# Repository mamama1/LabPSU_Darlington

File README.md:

# LabPSU_Darlington

Welcome to my Lab PSU project, which is based on a pair of BD139/TIP3055 Darlingtons and the Teensy 3.5 (3.6 should work as well).<br><br>

This project has been heavily inspired by the original µSupply project by Dave Jones from the EEVBlog.<br>
Link: https://www.eevblog.com/projects/usupply/ <br><br>

Specs:<br>
0 - 16.384V output controllable in 1mV steps<br>
0 - 4096 mA output controllable in 1mA steps<br>
Around 0.1% accuracy due to high accuracy components<br>
16 Bit DACs (DAC8311)<br>
High precision voltage reference for the DACs (REF5040)
16 Bit ADCs (ADS1115)<br>
Low Ripple, Low Noise<br>
25kHz PWM/temperature controlled Fan output for standard PWM capable FANs<br>
One Board solution (toroidal transformer not onboard)<br>
Optional Front Panel for Display, rotary encoder, button and LED mounting<br>
Fast UI thanks to Teensy's 120 MHz frequency<br>
Header for ESP8266, ESP32 or basically any other UART compatible device, including 3.3V and GND as well as two I/O pins (one PWM capable)

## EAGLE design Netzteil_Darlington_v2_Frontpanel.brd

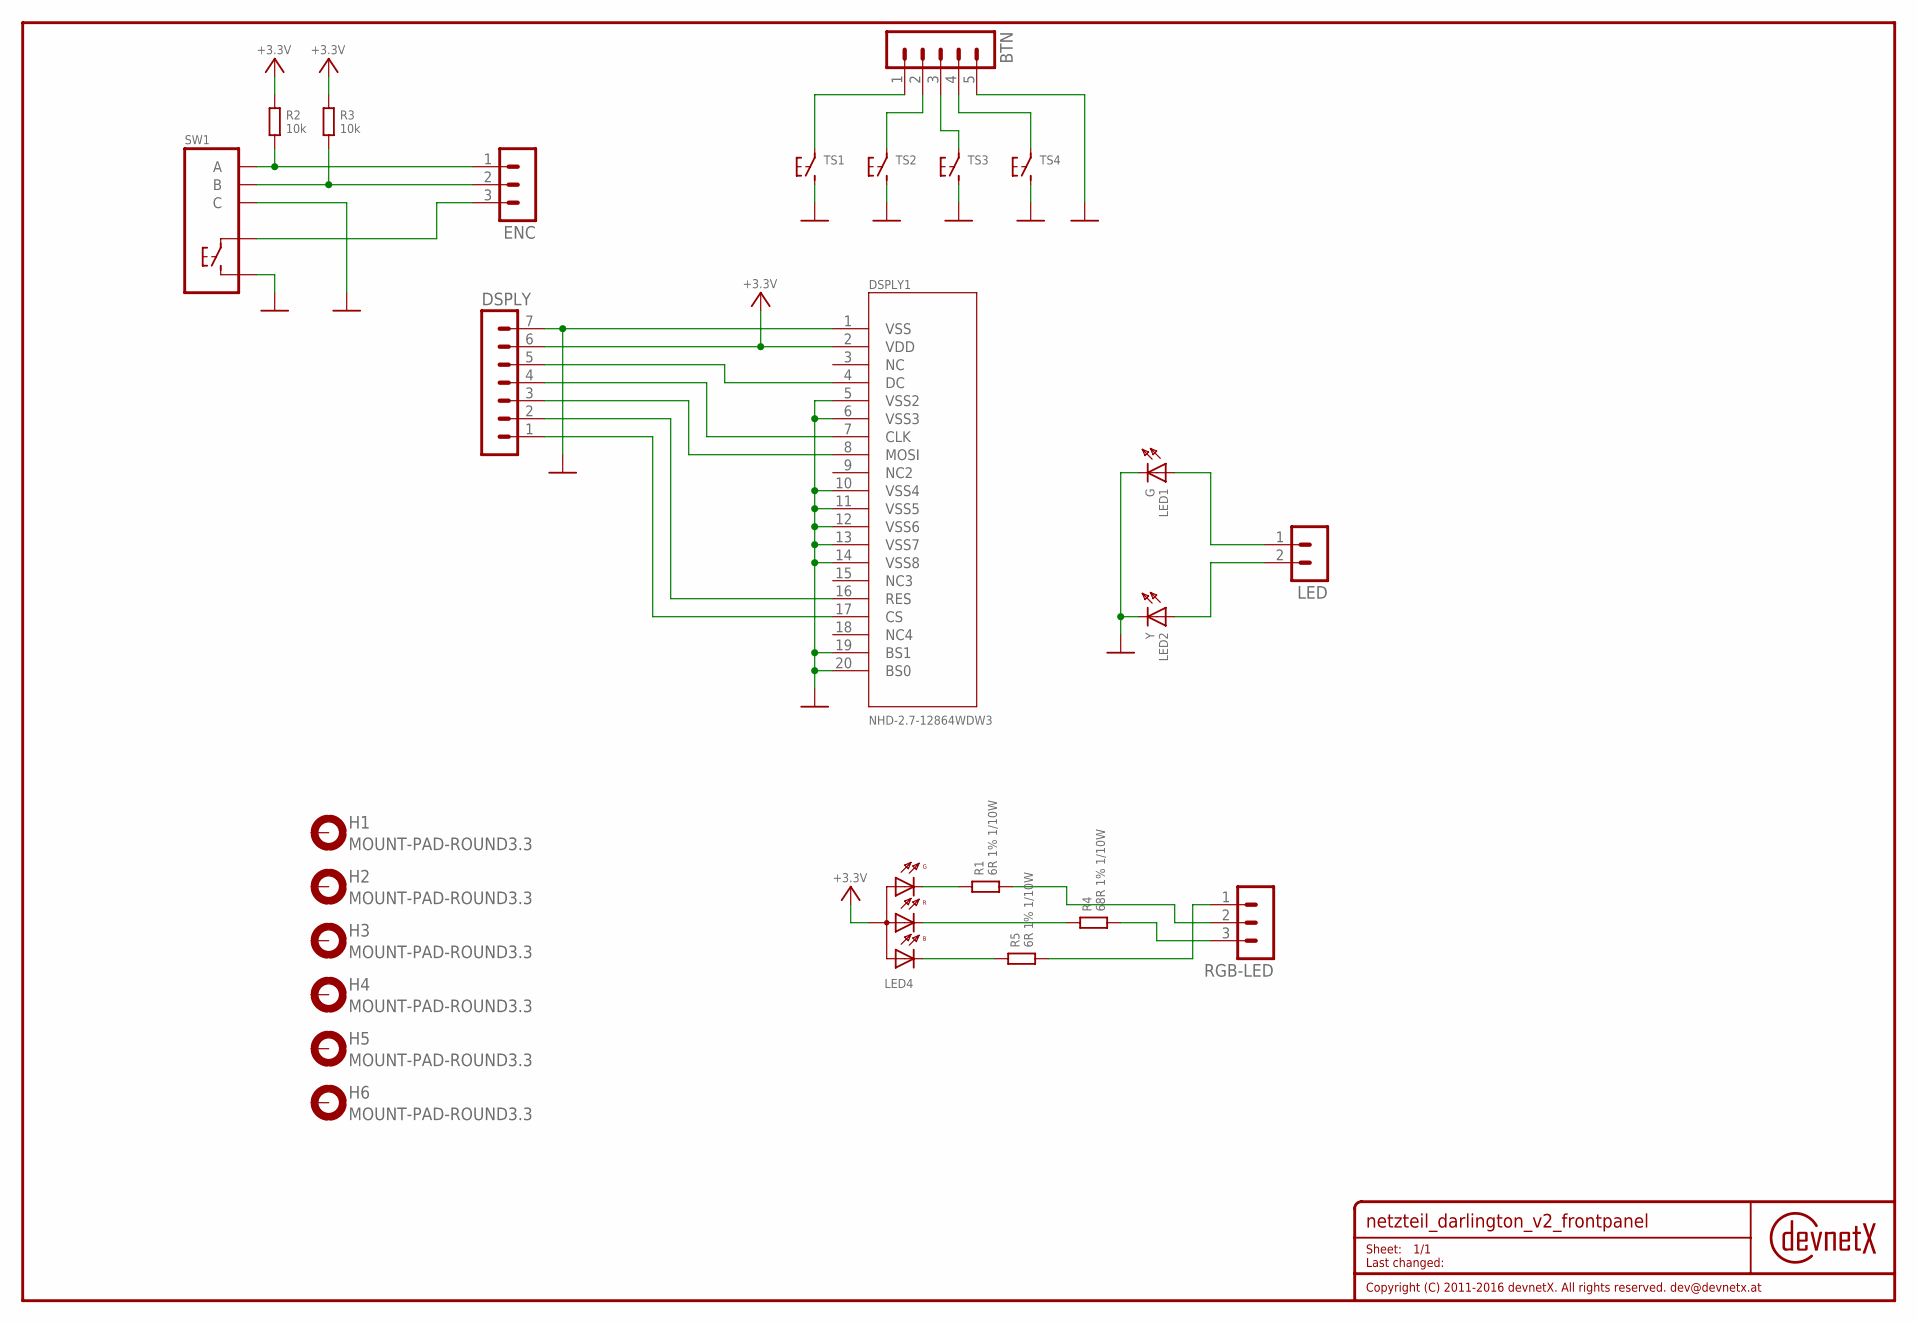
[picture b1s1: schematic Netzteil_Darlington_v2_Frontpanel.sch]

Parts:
BTN: JST-PH-2.0-5P
DNX-NAME-1: DOC-R1.27; DRAWINGNAME-1.27
DSPLY: JST-PH-2.0-7P
DSPLY1: NHD-2.7-12864WDW3
ENC: JST-PH-2.0-3P
H1, H2, H3, H4, H5, H6: MOUNT-PAD-ROUND3.3; 3,3-PAD
LED: JST-PH-2.0-2P
LED1: G; LED0805
LED2: Y; LED0805
LED4: LED-RGB; C1411
R1, R5: 6R 1% 1/10W; C0805K
R2, R3: 10k; C0805K
R4: 68R 1% 1/10W; C0805K
RGB-LED: JST-PH-2.0-3P
SW1: EC12E-SW
TS1, TS2, TS3, TS4: TS1B3F-10XX; B3F-10XX

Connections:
+3.3V: DSPLY.6, DSPLY1.2 (VDD), LED4.1 (A), R2.1, R3.1
unnamed: LED.1, LED1.A
unnamed: LED.2, LED2.A
unnamed: DSPLY.5, DSPLY1.4 (DC)
unnamed: BTN.1, TS1.1
unnamed: ENC.1, R2.2, SW1.A
unnamed: DSPLY.4, DSPLY1.7 (CLK)
unnamed: DSPLY.3, DSPLY1.8 (MOSI)
unnamed: LED4.4 (C4), R1.1
unnamed: ENC.2, R3.2, SW1.B
unnamed: ENC.3, SW1.1
unnamed: BTN.2, TS2.1
unnamed: BTN.3, TS3.1
unnamed: BTN.4, TS4.1
unnamed: LED4.3 (C3), R4.1
unnamed: DSPLY.2, DSPLY1.16 (RES)
unnamed: DSPLY.1, DSPLY1.17 (CS)
unnamed: LED4.2 (C2), R5.1
unnamed: R5.2, RGB-LED.1
unnamed: R4.2, RGB-LED.3
unnamed: R1.2, RGB-LED.2
VSS: BTN.5, DSPLY.7, DSPLY1.1 (VSS), DSPLY1.5 (VSS2), DSPLY1.6 (VSS3), DSPLY1.10 (VSS4), DSPLY1.11 (VSS5), DSPLY1.12 (VSS6), DSPLY1.13 (VSS7), DSPLY1.14 (VSS8), DSPLY1.19 (BS1), DSPLY1.20 (BS0), LED1.C, LED2.C, SW1.2, SW1.C, TS1.3 (2), TS2.3 (2), TS3.3 (2), TS4.3 (2)

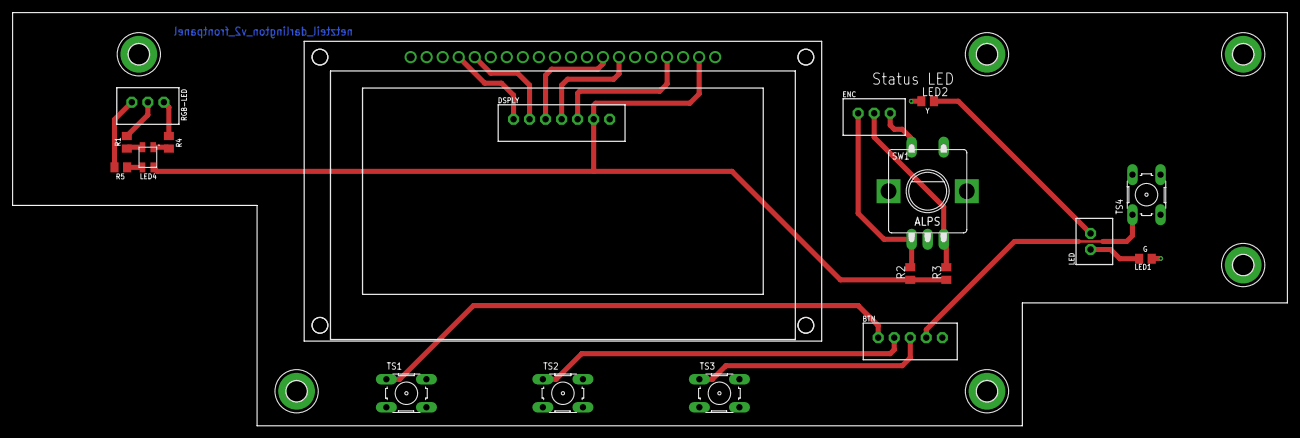
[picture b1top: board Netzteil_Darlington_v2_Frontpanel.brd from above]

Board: 2 copper layers, 202.0 x 65.5 mm, 26 parts (0 on the bottom side), 22 nets.

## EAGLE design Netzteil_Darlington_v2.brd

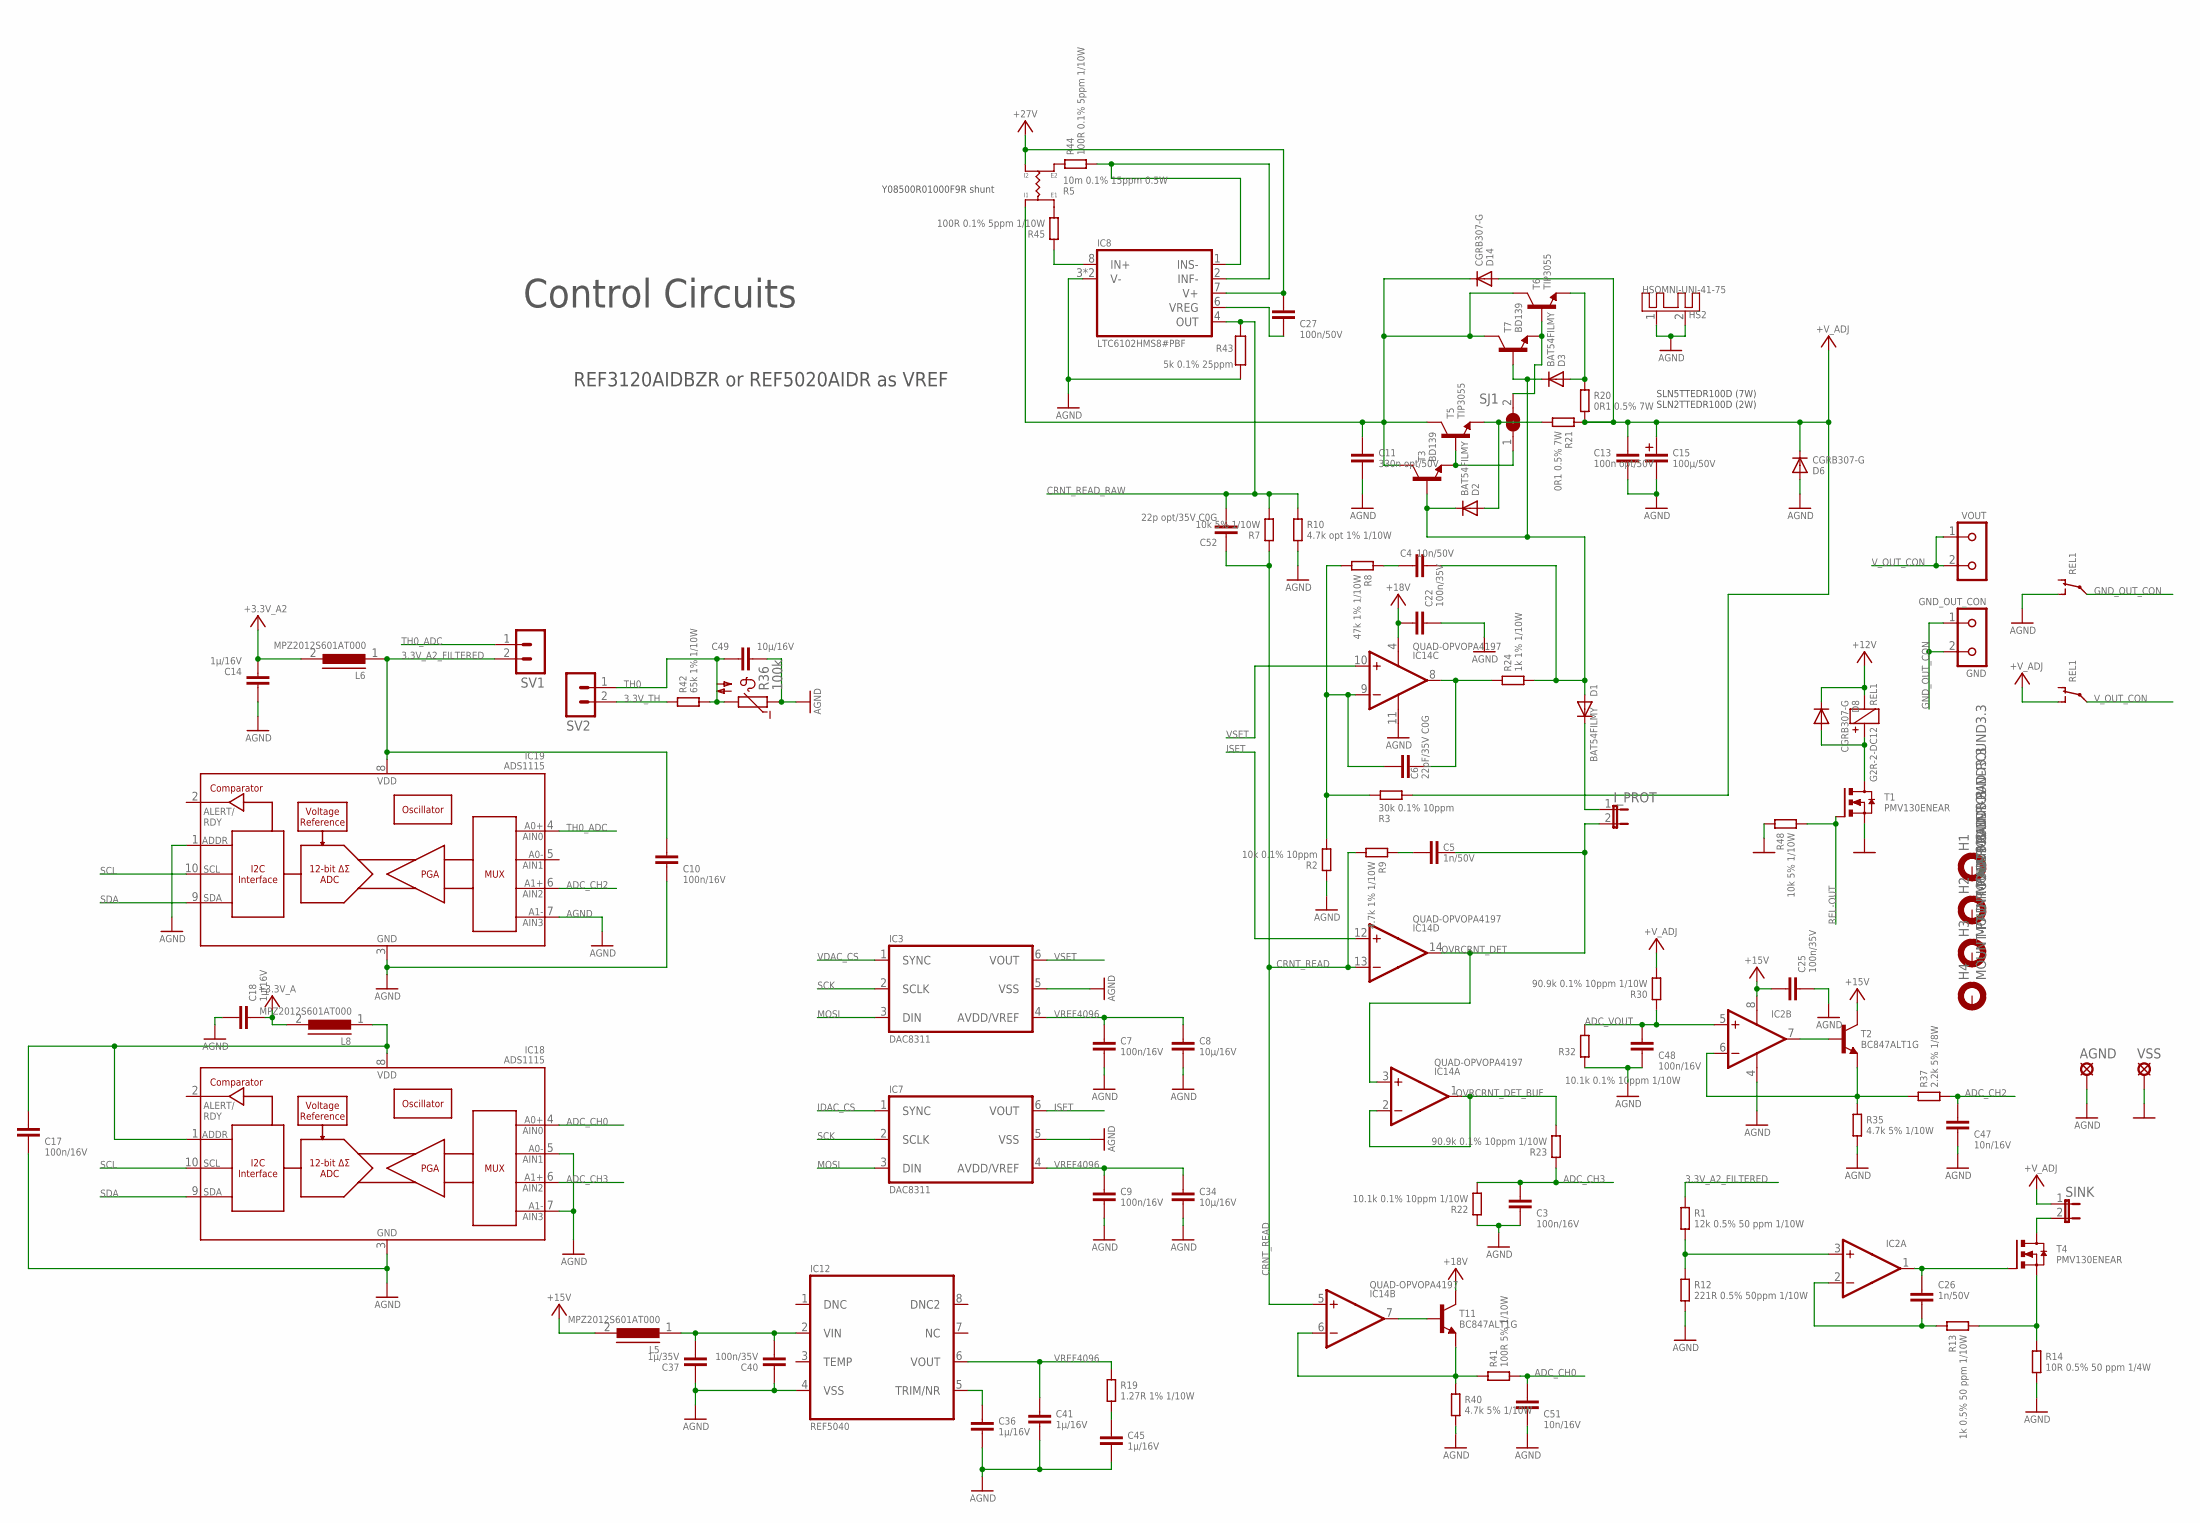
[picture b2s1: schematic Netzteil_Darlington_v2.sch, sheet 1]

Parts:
AGND: LSP13
C3, C7, C9, C10, C17, C48: 100n/16V; 0805
C4: 10n/50V; 0805
C5, C26: 1n/50V; 0805
C6: 22pF/35V C0G; 0805
C8, C34, C49: 10µ/16V; 1206
C11: 330n opt/50V; 0805
C13: 100n opt/50V; 0805
C14, C18, C36, C41, C45: 1µ/16V; 0805
C15: 100µ/50V; C+/3.5/8
C22, C25, C40: 100n/35V; 0805
C27: 100n/50V; 0805
C37: 1µ/35V; 0805
C47, C51: 10n/16V; 0805
C52: 22p opt/35V C0G; 0805
D1, D2, D3: BAT54FILMY; SOT23
D6, D8, D14: CGRB307-G; DO214AA-CGRB307-G
GND_OUT_CON: GND; KL2-691311500002
H1, H2, H3, H4: MOUNT-PAD-ROUND3.3; 3,3-PAD
HS2: HSOMNI-UNI-41-75; OMNI-UNI-41-75
IC2: DUAL-OPVSOP8; SOP8
IC3, IC7: DAC8311; SC-70-6
IC8: LTC6102HMS8#PBF; MSOP8-0.65-3X3MM
IC12: REF5040; MSOP8-0.65-3X3MM
IC14: QUAD-OPVOPA4197; SO14
IC18, IC19: ADS1115; MSOP10
I_PROT: JP1E; JP1
L5, L6, L8: MPZ2012S601AT000; C0805K
R1: 12k 0.5% 50 ppm 1/10W; C0805K
R2: 10k 0.1% 10ppm; C0805K
R3: 30k 0.1% 10ppm; C0805K
R5: 10m 0.1% 15ppm 0.5W; CSM2512
R7, R48: 10k 5% 1/10W; C0805K
R8: 47k 1% 1/10W; C0805K
R9: 4.7k 1% 1/10W; C0805K
R10: 4.7k opt 1% 1/10W; C0805K
R12: 221R 0.5% 50ppm 1/10W; C0805K
R13: 1k 0.5% 50 ppm 1/10W; C0805K
R14: 10R 0.5% 50 ppm 1/4W; C0805K
R19: 1.27R 1% 1/10W; C0805K
R20, R21: 0R1 0.5% 7W; SLN2
R22, R32: 10.1k 0.1% 10ppm 1/10W; C0805K
R23, R30: 90.9k 0.1% 10ppm 1/10W; C0805K
R24: 1k 1% 1/10W; C0805K
R35, R40: 4.7k 5% 1/10W; C0805K
R36: 100k; P640
R37: 2.2k 5% 1/8W; C0805K
R41: 100R 5% 1/10W; C0805K
R42: 65k 1% 1/10W; C0805K
R43: 5k 0.1% 25ppm; R1206
R44, R45: 100R 0.1% 5ppm 1/10W; C0805K
REL1: G2R-2-DC12; REL-G2R2
SINK: JP1E; JP1
SJ1: SJ
SV1, SV2: JST-PH-2.0-2P
T1, T4: PMV130ENEAR; SOT23
T2, T11: BC847ALT1G; SOT23-BEC
T3, T7: BD139; TO126
T5, T6: TIP3055; TOP3AV
VOUT: KL2691311500002; KL2-691311500002
VSS: LSP13

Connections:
3.3V_TH: R42.1, SV2.2; also elsewhere on the board
+3.3V_A: C18.2, L8.2; also elsewhere on the board
+3.3V_A2: C14.2, L6.2; also elsewhere on the board
+12V: D8.C, REL1.-; also elsewhere on the board
+18V: C22.1, IC14.4 (V+), T11.C; also elsewhere on the board
+27V: C27.1, IC8.7 (V+), R5.I2; also elsewhere on the board
+V_ADJ: C13.1, C15.+, D6.C, D14.A, R3.1, R20.2, R21.1, R30.2, REL1.S1 (S), SINK.1
ADC_CH0: C51.1, IC18.4 (AIN0), R41.2
ADC_CH2: C47.1, IC19.6 (AIN2), R37.2
ADC_CH3: C3.1, IC18.6 (AIN2), R22.2, R23.1
ADC_VOUT: C48.1, IC2.5 (+IN), R30.1, R32.2
AGND: AGND.MP, C3.2, C7.2, C8.2, C9.2, C10.2, C11.2, C13.2, C14.1, C15.-, C17.2, C18.1, C22.2, C25.2, C34.2, C36.2, C37.1, C40.1, C41.2, C45.2, C47.2, C48.2, C49.1, C51.2, D6.A, HS2.1, HS2.2, IC2.4 (V-), IC3.5 (VSS), IC7.5 (VSS), IC8.3 (V-), IC8.5 (V-), IC12.4 (VSS), IC14.11 (V-), IC18.3 (VSS), IC18.5 (AIN1), IC18.7 (AIN3), IC19.1 (ADDR), IC19.3 (VSS), IC19.7 (AIN3), R2.1, R10.2, R12.2, R14.2, R22.1, R32.1, R35.2, R36.1, R40.2, R43.1, REL1.S2 (S); also elsewhere on the board
CRNT_READ: C52.1, IC14.5 (+IN), IC14.13 (-IN), R7.1, R9.2
CRNT_READ_RAW: C52.2, IC8.4 (OUT), R7.2, R10.1, R43.2
GND_OUT_CON: GND_OUT_CON.1, GND_OUT_CON.2, REL1.P2
IDAC_CS: IC7.1 (SYNC); also elsewhere on the board
ISET: IC7.6 (VOUT), IC14.12 (+IN)
MOSI: IC3.3 (DIN), IC7.3 (DIN); also elsewhere on the board
unnamed: C11.1, D14.C, R5.I1, T3.2 (C), T5.C, T6.C, T7.2 (C)
unnamed: D3.1 (A), R20.1, T6.E
unnamed: SJ1.2, T6.B, T7.1 (E)
unnamed: IC14.7 (OUT), T11.B
unnamed: D2.1 (A), R21.2, T5.E
unnamed: D1.3 (C), I_PROT.1
unnamed: IC2.3 (+IN), R1.2, R12.1
unnamed: C36.1, IC12.5 (TRIM/NR)
unnamed: SJ1.1, T3.1 (E), T5.B
unnamed: R13.2, R14.1, T4.2 (S)
unnamed: C26.2, IC2.2 (-IN), R13.1
unnamed: C6.2, IC14.8 (OUT), R24.1
unnamed: C4.2, D1.1 (A), D2.3 (C), D3.3 (C), R24.2, T3.3 (B), T7.3 (B)
unnamed: C17.1, IC18.1 (ADDR), IC18.8 (VDD), L8.1
unnamed: C37.2, C40.2, IC12.2 (VIN), L5.1
unnamed: C4.1, R8.1
unnamed: C5.1, R9.1
unnamed: C6.1, IC14.9 (-IN), R2.2, R3.2, R8.2
unnamed: C45.1, R19.2
unnamed: C26.1, IC2.1 (OUT), T4.1 (G)
unnamed: SINK.2, T4.3 (D)
unnamed: D8.A, REL1.+, T1.3 (D)
unnamed: IC2.6 (-IN), R35.1, R37.1, T2.E
unnamed: IC14.6 (-IN), R40.1, R41.1, T11.E
unnamed: IC8.8 (IN+), R45.1
unnamed: IC8.1 (INS-), IC8.2 (INF-), R44.2
unnamed: C27.2, IC8.6 (VREG)
unnamed: R5.E2, R44.1
unnamed: R5.E1, R45.2
OVRCRNT_DET: C5.2, IC14.3 (+IN), IC14.14 (OUT), I_PROT.2
OVRCRNT_DET_BUF: IC14.1 (OUT), IC14.2 (-IN), R23.2
REL-OUT: R48.2, T1.1 (G); also elsewhere on the board
SCK: IC3.2 (SCLK), IC7.2 (SCLK); also elsewhere on the board
SCL: IC18.10 (SCL), IC19.10 (SCL); also elsewhere on the board
SDA: IC18.9 (SDA), IC19.9 (SDA); also elsewhere on the board
TH0: C49.2, R36.2, R42.2, SV2.1; also elsewhere on the board
TH0_ADC: IC19.4 (AIN0), SV1.1; also elsewhere on the board
VDAC_CS: IC3.1 (SYNC); also elsewhere on the board
VREF4096: C7.1, C8.1, C9.1, C34.1, C41.1, IC3.4 (AVDD/VREF), IC7.4 (AVDD/VREF), IC12.6 (VOUT), R19.1
VSET: IC3.6 (VOUT), IC14.10 (+IN)
VSS: R48.1, T1.2 (S), VSS.MP; also elsewhere on the board
V_OUT_CON: REL1.P1, VOUT.1, VOUT.2

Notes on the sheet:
Control Circuits
SLN5TTEDR100D (7W) SLN2TTEDR100D (2W)
REF3120AIDBZR or REF5020AIDR as VREF
Y08500R01000F9R shunt

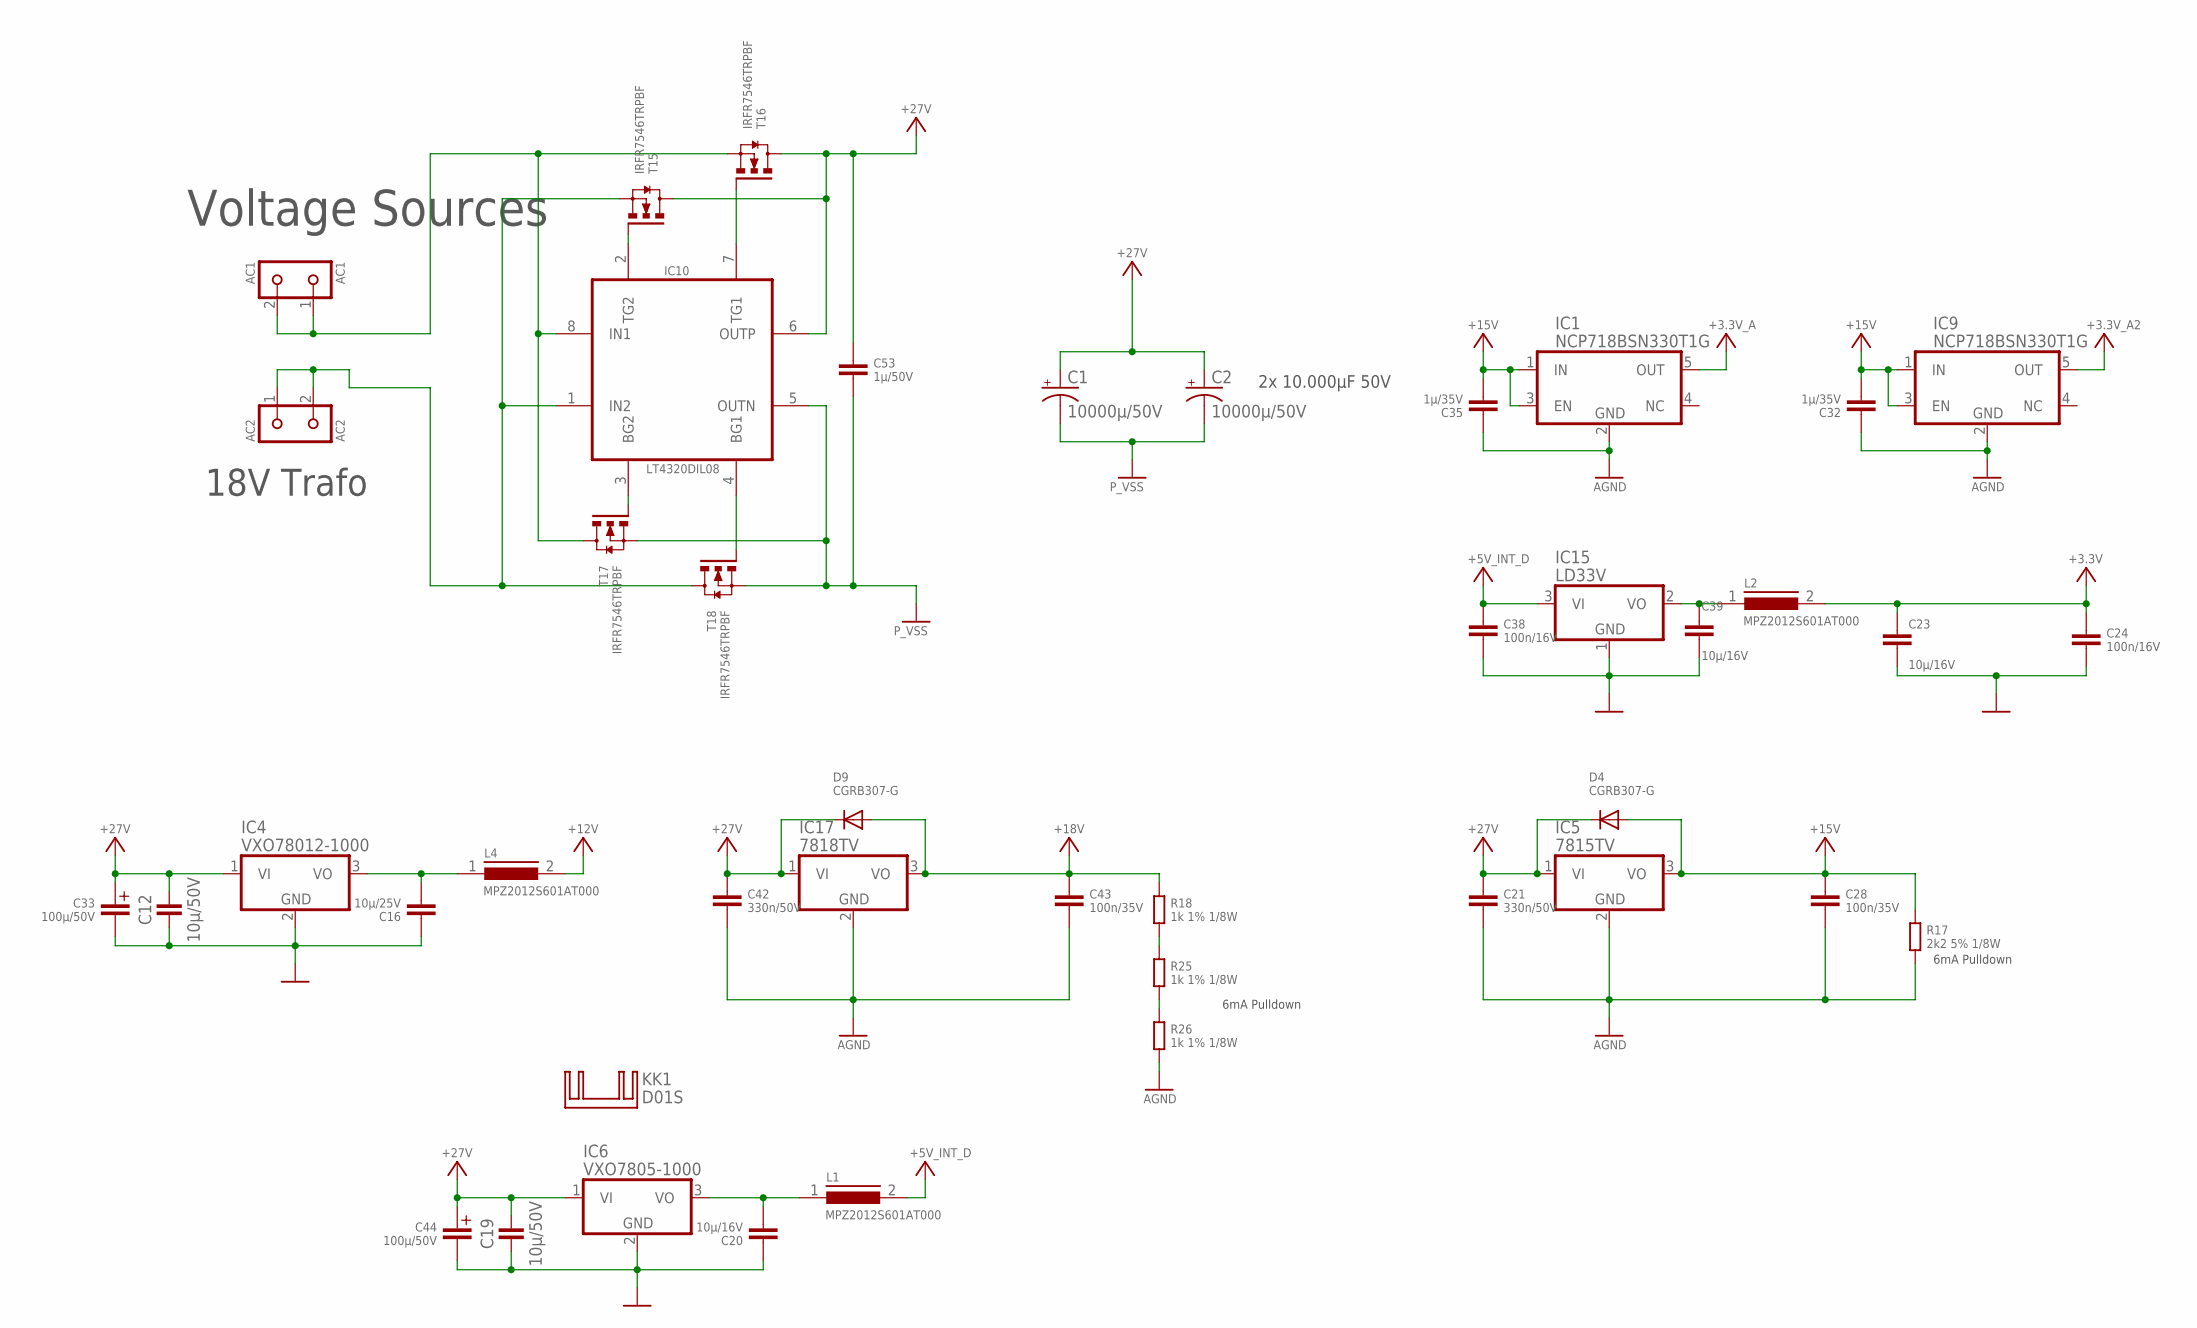
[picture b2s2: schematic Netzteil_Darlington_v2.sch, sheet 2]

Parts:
AC1: AC1; KL2-691311500002
AC2: AC2; KL2-691311500002
C1, C2: 10000µ/50V; EB22,5D
C12, C19: 10µ/50V; C1210
C16: 10µ/25V; 1206
C20, C23, C39: 10µ/16V; 1206
C21, C42: 330n/50V; 0805
C24, C38: 100n/16V; 0805
C28, C43: 100n/35V; 0805
C32, C35: 1µ/35V; 0805
C33, C44: 100µ/50V; C+/3.5/8
C53: 1µ/50V; 1206
D4, D9: CGRB307-G; DO214AA-CGRB307-G
IC1, IC9: NCP718BSN330T1G; SOT23-5
IC4: VXO78012-1000; 78XX-DC-DC
IC5: 7815TV; TO220V
IC6: VXO7805-1000; 78XX-DC-DC
IC10: LT4320DIL08; DIL08
IC15: LD33V; TO220V
IC17: 7818TV; TO220V
KK1: D01S
L1, L2, L4: MPZ2012S601AT000; C0805K
R17: 2k2 5% 1/8W; C0805K
R18, R25, R26: 1k 1% 1/8W; C0805K
T15, T16, T17, T18: IRFR7546TRPBF; DPACK

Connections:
+3.3V: C23.1, C24.1, L2.2; also elsewhere on the board
+3.3V_A: IC1.5 (OUT); also elsewhere on the board
+3.3V_A2: IC9.5 (OUT); also elsewhere on the board
+5V_INT_D: C38.1, IC15.3 (VI), L1.2; also elsewhere on the board
+12V: L4.2; also elsewhere on the board
+18V: C43.1, D9.A, IC17.3 (VO), R18.1; also elsewhere on the board
+27V: C1.+, C2.+, C12.2, C19.2, C21.1, C33.+, C42.1, C44.+, C53.1, D4.C, D9.C, IC4.1 (VI), IC5.1 (VI), IC6.1 (VI), IC10.6 (OUTP), IC17.1 (VI), T15.3 (D), T16.3 (D); also elsewhere on the board
AGND: C21.2, C28.2, C32.1, C35.1, C42.2, C43.2, IC1.2 (GND), IC5.2 (GND), IC9.2 (GND), IC17.2 (GND), R17.2, R26.2; also elsewhere on the board
unnamed: C20.2, IC6.3 (VO), L1.1
unnamed: AC2.1, AC2.2, IC10.1 (IN2), T15.2 (S), T18.3 (D)
unnamed: C16.2, IC4.3 (VO), L4.1
unnamed: R18.2, R25.1
unnamed: R25.2, R26.1
unnamed: C39.2, IC15.2 (VO), L2.1
unnamed: IC10.2 (TG2), T15.1 (G)
unnamed: IC10.3 (BG2), T17.1 (G)
unnamed: IC10.7 (TG1), T16.1 (G)
unnamed: IC10.4 (BG1), T18.1 (G)
unnamed: AC1.1, AC1.2, IC10.8 (IN1), T16.2 (S), T17.3 (D)
P_VSS: C1.-, C2.-, C53.2, IC10.5 (OUTN), T17.2 (S), T18.2 (S)
VSS: C12.1, C16.1, C19.1, C20.1, C23.2, C24.2, C33.-, C38.2, C39.1, C44.-, IC4.2 (GND), IC6.2 (GND), IC15.1 (GND); also elsewhere on the board

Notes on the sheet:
2x 10.000µF 50V
Voltage Sources
18V Trafo
6mA Pulldown

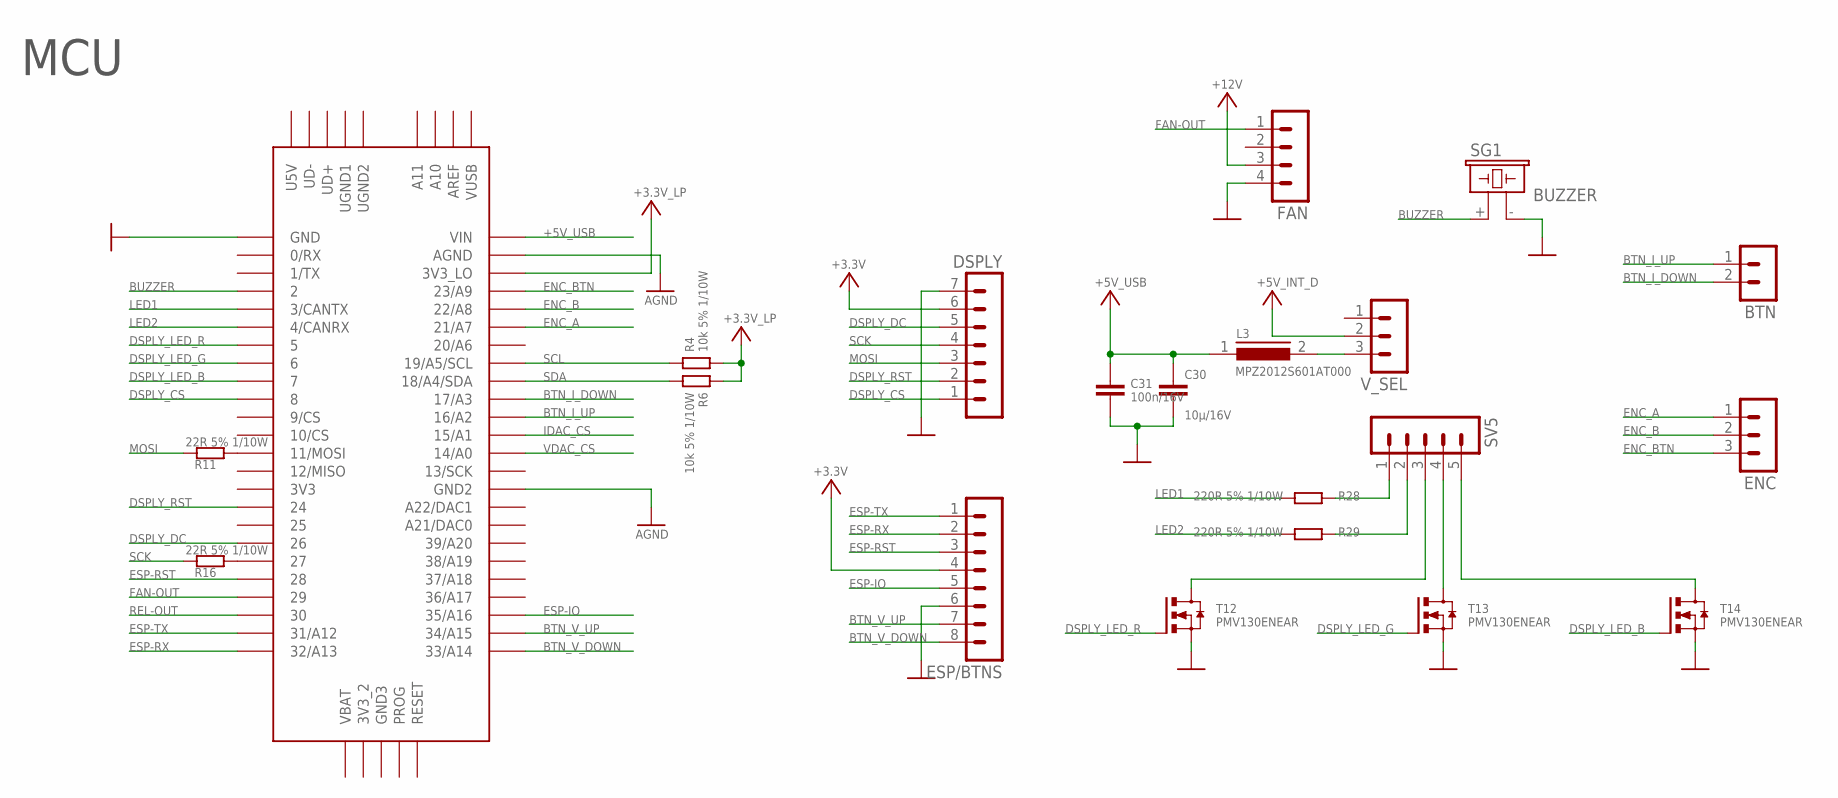
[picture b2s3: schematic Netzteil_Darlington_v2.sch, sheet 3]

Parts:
BTN: JST-PH-2.0-2P
C30: 10µ/16V; 1206
C31: 100n/16V; 0805
DSPLY: JST-PH-2.0-7P
ENC: JST-PH-2.0-3P
ESP/BTNS: JST-PH-2.0-8P
FAN: JST-PH-2.0-4P
L3: MPZ2012S601AT000; C0805K
R4, R6: 10k 5% 1/10W; C0805K
R11, R16: 22R 5% 1/10W; C0805K
R28, R29: 220R 5% 1/10W; C0805K
SG1: BUZZER; 254-EMB73-RO
SV5: JST-PH-2.0-5P
T12, T13, T14: PMV130ENEAR; SOT23
U$33: TEENSY_3.5/3.6
V_SEL: MA03-1

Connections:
+3.3V: DSPLY.6, ESP/BTNS.4; also elsewhere on the board
+3.3V_LP: R4.2, R6.1, U$33.3V3_LO
+5V_INT_D: V_SEL.2; also elsewhere on the board
+5V_USB: C30.1, C31.1, L3.1, U$33.VIN
+12V: FAN.3; also elsewhere on the board
AGND: U$33.AGND, U$33.GND2; also elsewhere on the board
BTN1: BTN.2, U$33.17/A3
BTN2: BTN.1, U$33.16/A2
BTN3: ESP/BTNS.8, U$33.33/A14
BTN4: ESP/BTNS.7, U$33.34/A15
BUZZER: SG1.+ (1), U$33.2
DSPLY_CS: DSPLY.1, U$33.8
DSPLY_DC: DSPLY.5, U$33.26
DSPLY_LED_B: T14.1 (G), U$33.7
DSPLY_LED_G: T13.1 (G), U$33.6
DSPLY_LED_R: T12.1 (G), U$33.5
DSPLY_RST: DSPLY.2, U$33.24
ENC_A: ENC.1, U$33.21/A7
ENC_B: ENC.2, U$33.22/A8
ENC_BTN: ENC.3, U$33.23/A9
ESP-IO: ESP/BTNS.5, U$33.35/A16
ESP-RST: ESP/BTNS.3, U$33.28
ESP-RX: ESP/BTNS.2, U$33.32/A13
ESP-TX: ESP/BTNS.1, U$33.31/A12
FAN-OUT: FAN.1, U$33.29
IDAC_CS: U$33.15/A1; also elsewhere on the board
LED1: R28.1, U$33.3/CANTX
LED2: R29.1, U$33.4/CANRX
MOSI: DSPLY.3, R11.1; also elsewhere on the board
unnamed 49: SV5.3, T12.3 (D); also elsewhere on the board
unnamed: R16.2, U$33.27
unnamed: R11.2, U$33.11/MOSI
unnamed 60: R28.2, SV5.1; also elsewhere on the board
unnamed 63: R29.2, SV5.2; also elsewhere on the board
unnamed: L3.2, V_SEL.3
unnamed 80: SV5.4, T13.3 (D); also elsewhere on the board
unnamed 82: SV5.5, T14.3 (D); also elsewhere on the board
REL-OUT: U$33.30; also elsewhere on the board
SCK: DSPLY.4, R16.1; also elsewhere on the board
SCL: R4.1, U$33.19/A5/SCL; also elsewhere on the board
SDA: R6.2, U$33.18/A4/SDA; also elsewhere on the board
VDAC_CS: U$33.14/A0; also elsewhere on the board
VSS: C30.2, C31.2, DSPLY.7, ESP/BTNS.6, FAN.4, SG1.- (2), T12.2 (S), T13.2 (S), T14.2 (S), U$33.GND; also elsewhere on the board

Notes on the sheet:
MCU

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

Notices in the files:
Hardware/Netzteil_Darlington_v2.brd:
© 2019 azzurro@ne-mail.net
parts and their libraries:
devnetx: Copyright (C) 2011-2016 devnetX. All rights reserved. dev@devnetx.at
